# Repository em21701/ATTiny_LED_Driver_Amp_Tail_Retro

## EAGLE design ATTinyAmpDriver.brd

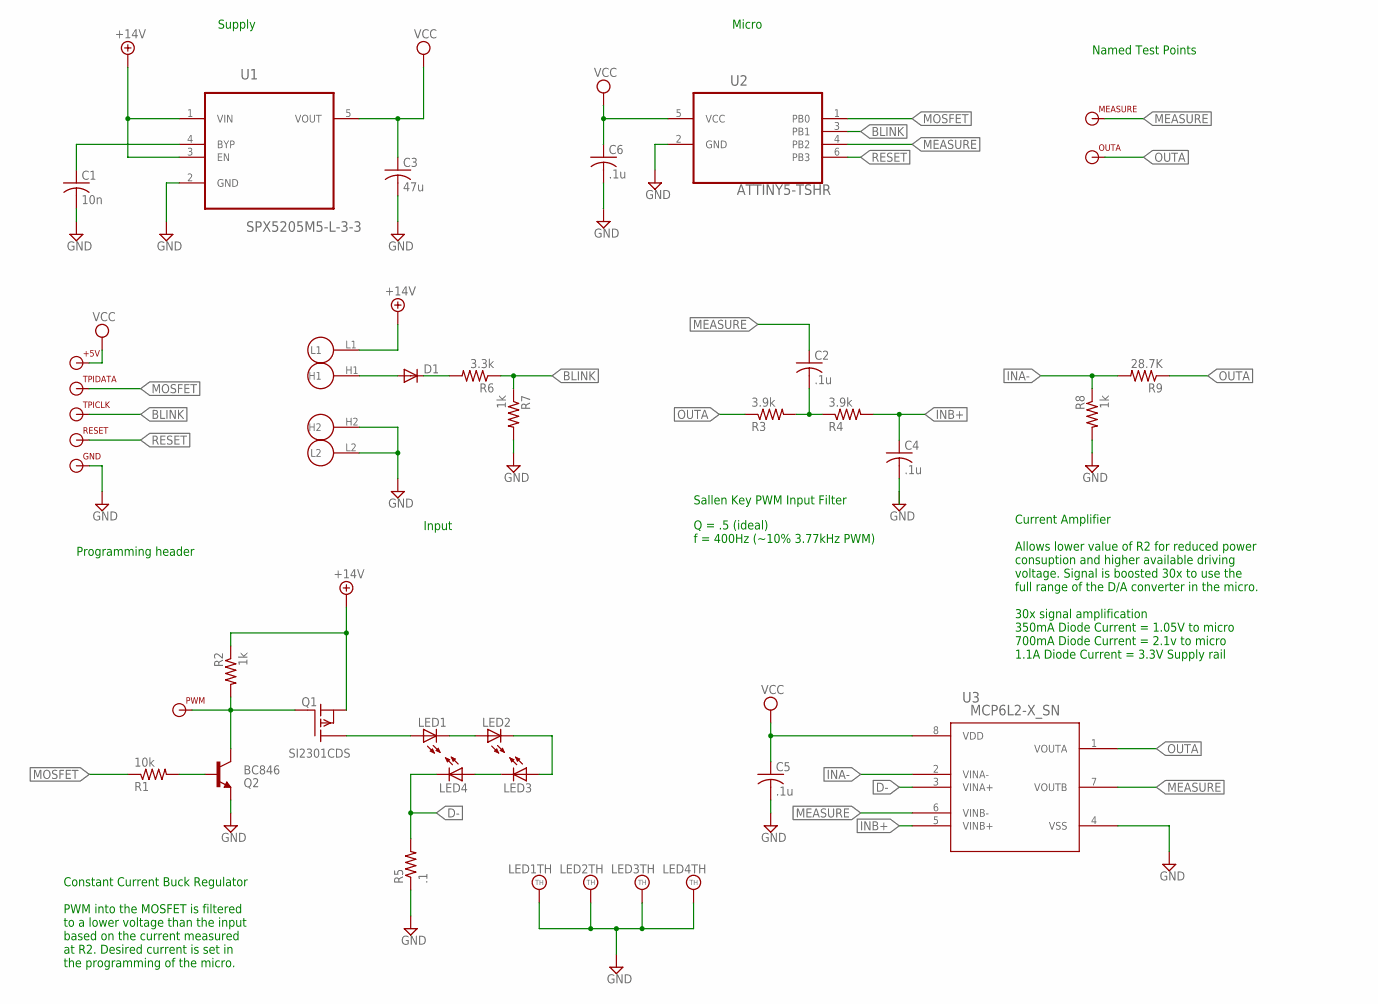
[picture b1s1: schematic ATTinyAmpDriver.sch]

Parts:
+5V: TPI; TPI_PAD
C1: 10n; C0603; DIGIKEY 445-1311-1-ND
C2, C4, C5, C6: .1u; C0603; DIGIKEY 445-1316-1-ND
C3: 47u; C1206; DIGIKEY 399-5508-1-ND
D1: DIODE_0603; D0603; DIGIKEY 641-1002-1-ND
GND: TPI; TPI_PAD
LED1, LED2, LED3, LED4: LUXEON_REBELCREE_XP-E; CREE_XP-E
MEASURE: TPI; TPI_PAD
OUTA: TPI; TPI_PAD
PWM: TPI; TPI_PAD
Q1: SI2301CDS; SOT-23_POWER; DIGIKEY 568-6956-1-ND
Q2: BC846; SOT23; DIGIKEY BC846BMTFCT-ND
R1: 10k; R0603; DIGIKEY RMCF0603FT10K0CT-ND
R2, R7, R8: 1k; R0603; DIGIKEY RMCF0603FT1K00CT-ND
R3, R4: 3.9k; R0603; DIGIKEY RMCF0603FT3K90CT-ND
R5: .1; R1206; DIGIKEY A103268CT-ND
R6: 3.3k; R0603; DIGIKEY RMCF0603FT3K30CT-ND
R9: 28.7K; R0603; DIGIKEY RMCF0603FT28R7CT-ND
RESET: TPI; TPI_PAD
TPICLK: TPI; TPI_PAD
TPIDATA: TPI; TPI_PAD
U1: SPX5205M5-L-3-3; SOT95P280X145-5N; DIGIKEY 1016-1251-ND
U2: ATTINY5-TSHR; SOT95P280X145-6N; DIGIKEY ATTINY10-TSHRCT-ND
U3: MCP6L2-X_SN; SOIC8-N_MC; DIGIKEY MCP6L2T-E/SNCT-ND
U$1: CON_TAILLIGHT; TAILLIGHT

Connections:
+14V: Q1.P$2 (S), R2.1, U1.1 (VIN), U1.3 (EN), U$1.L1
BLINK: R6.1, R7.1, TPICLK.P$1, U2.3 (PB1)
CROSSOVER: LED2.CT (C), LED3.AN (A)
D-: LED4.CT (C), R5.2, U3.3 (VINA+)
GND: C1.2, C3.2, C4.2, C5.2, C6.2, GND.P$1, LED1.TH, LED2.TH, LED3.TH, LED4.TH, Q2.2 (E), R5.1, R7.2, R8.2, U1.2 (GND), U2.2 (GND), U3.4 (VSS), U$1.H2, U$1.L2
INA-: R8.1, R9.2, U3.2 (VINA-)
INB+: C4.1, R4.2, U3.5 (VINB+)
MEASURE: C2.1, MEASURE.P$1, U2.4 (PB2), U3.6 (VINB-), U3.7 (VOUTB)
MOSFET: R1.1, TPIDATA.P$1, U2.1 (PB0)
unnamed: D1.1A (A), U$1.H1
unnamed: C1.1, U1.4 (BYP)
unnamed: LED1.AN (A), Q1.P$3 (D)
unnamed: D1.2C (C), R6.2
unnamed: PWM.P$1, Q1.P$1 (G), Q2.3 (C), R2.2
unnamed: Q2.1 (B), R1.2
unnamed: LED1.CT (C), LED2.AN (A)
unnamed: C2.2, R3.2, R4.1
unnamed: LED3.CT (C), LED4.AN (A)
OUTA: OUTA.P$1, R3.1, R9.1, U3.1 (VOUTA)
RESET: RESET.P$1, U2.6 (PB3)
VCC: +5V.P$1, C3.1, C5.1, C6.1, U1.5 (VOUT), U2.5 (VCC), U3.8 (VDD)

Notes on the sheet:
Supply
Micro
Input
Programming header
Current Amplifier Allows lower value of R2 for reduced power consuption and higher available driving voltage. Signal is boosted 30x to use the full range of the D/A converter in the micro. 30x signal amplification 350mA Diode Current = 1.05V to micro 700mA Diode Current = 2.1v to micro 1.1A Diode C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
Constant Current Buck Regulator PWM into the MOSFET is filtered to a lower voltage than the input based on the current measured at R2. Desired current is set in the programming of the micro.
Sallen Key PWM Input Filter
Q = .5 (ideal) f = 400Hz (~10% 3.77kHz PWM)
Named Test Points

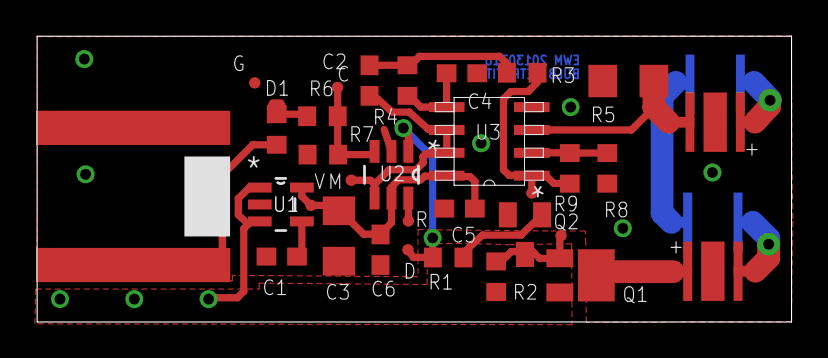
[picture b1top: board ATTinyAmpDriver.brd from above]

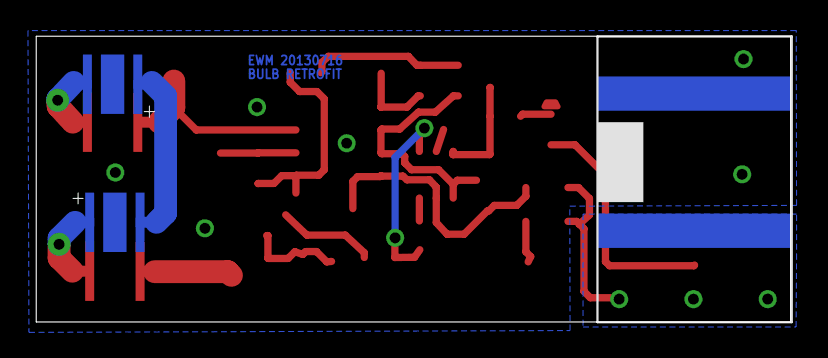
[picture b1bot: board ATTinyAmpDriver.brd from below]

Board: 2 copper layers, 41.9 x 15.9 mm, 34 parts (3 on the bottom side), 21 nets.

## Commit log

2013-07-16 Board Complete
2013-07-16 File Cleanup
2013-07-17 Fixed pin polarity on Tail Connecter
2013-07-25 Created programming fixture
2013-08-06 Updated masks & programmer
